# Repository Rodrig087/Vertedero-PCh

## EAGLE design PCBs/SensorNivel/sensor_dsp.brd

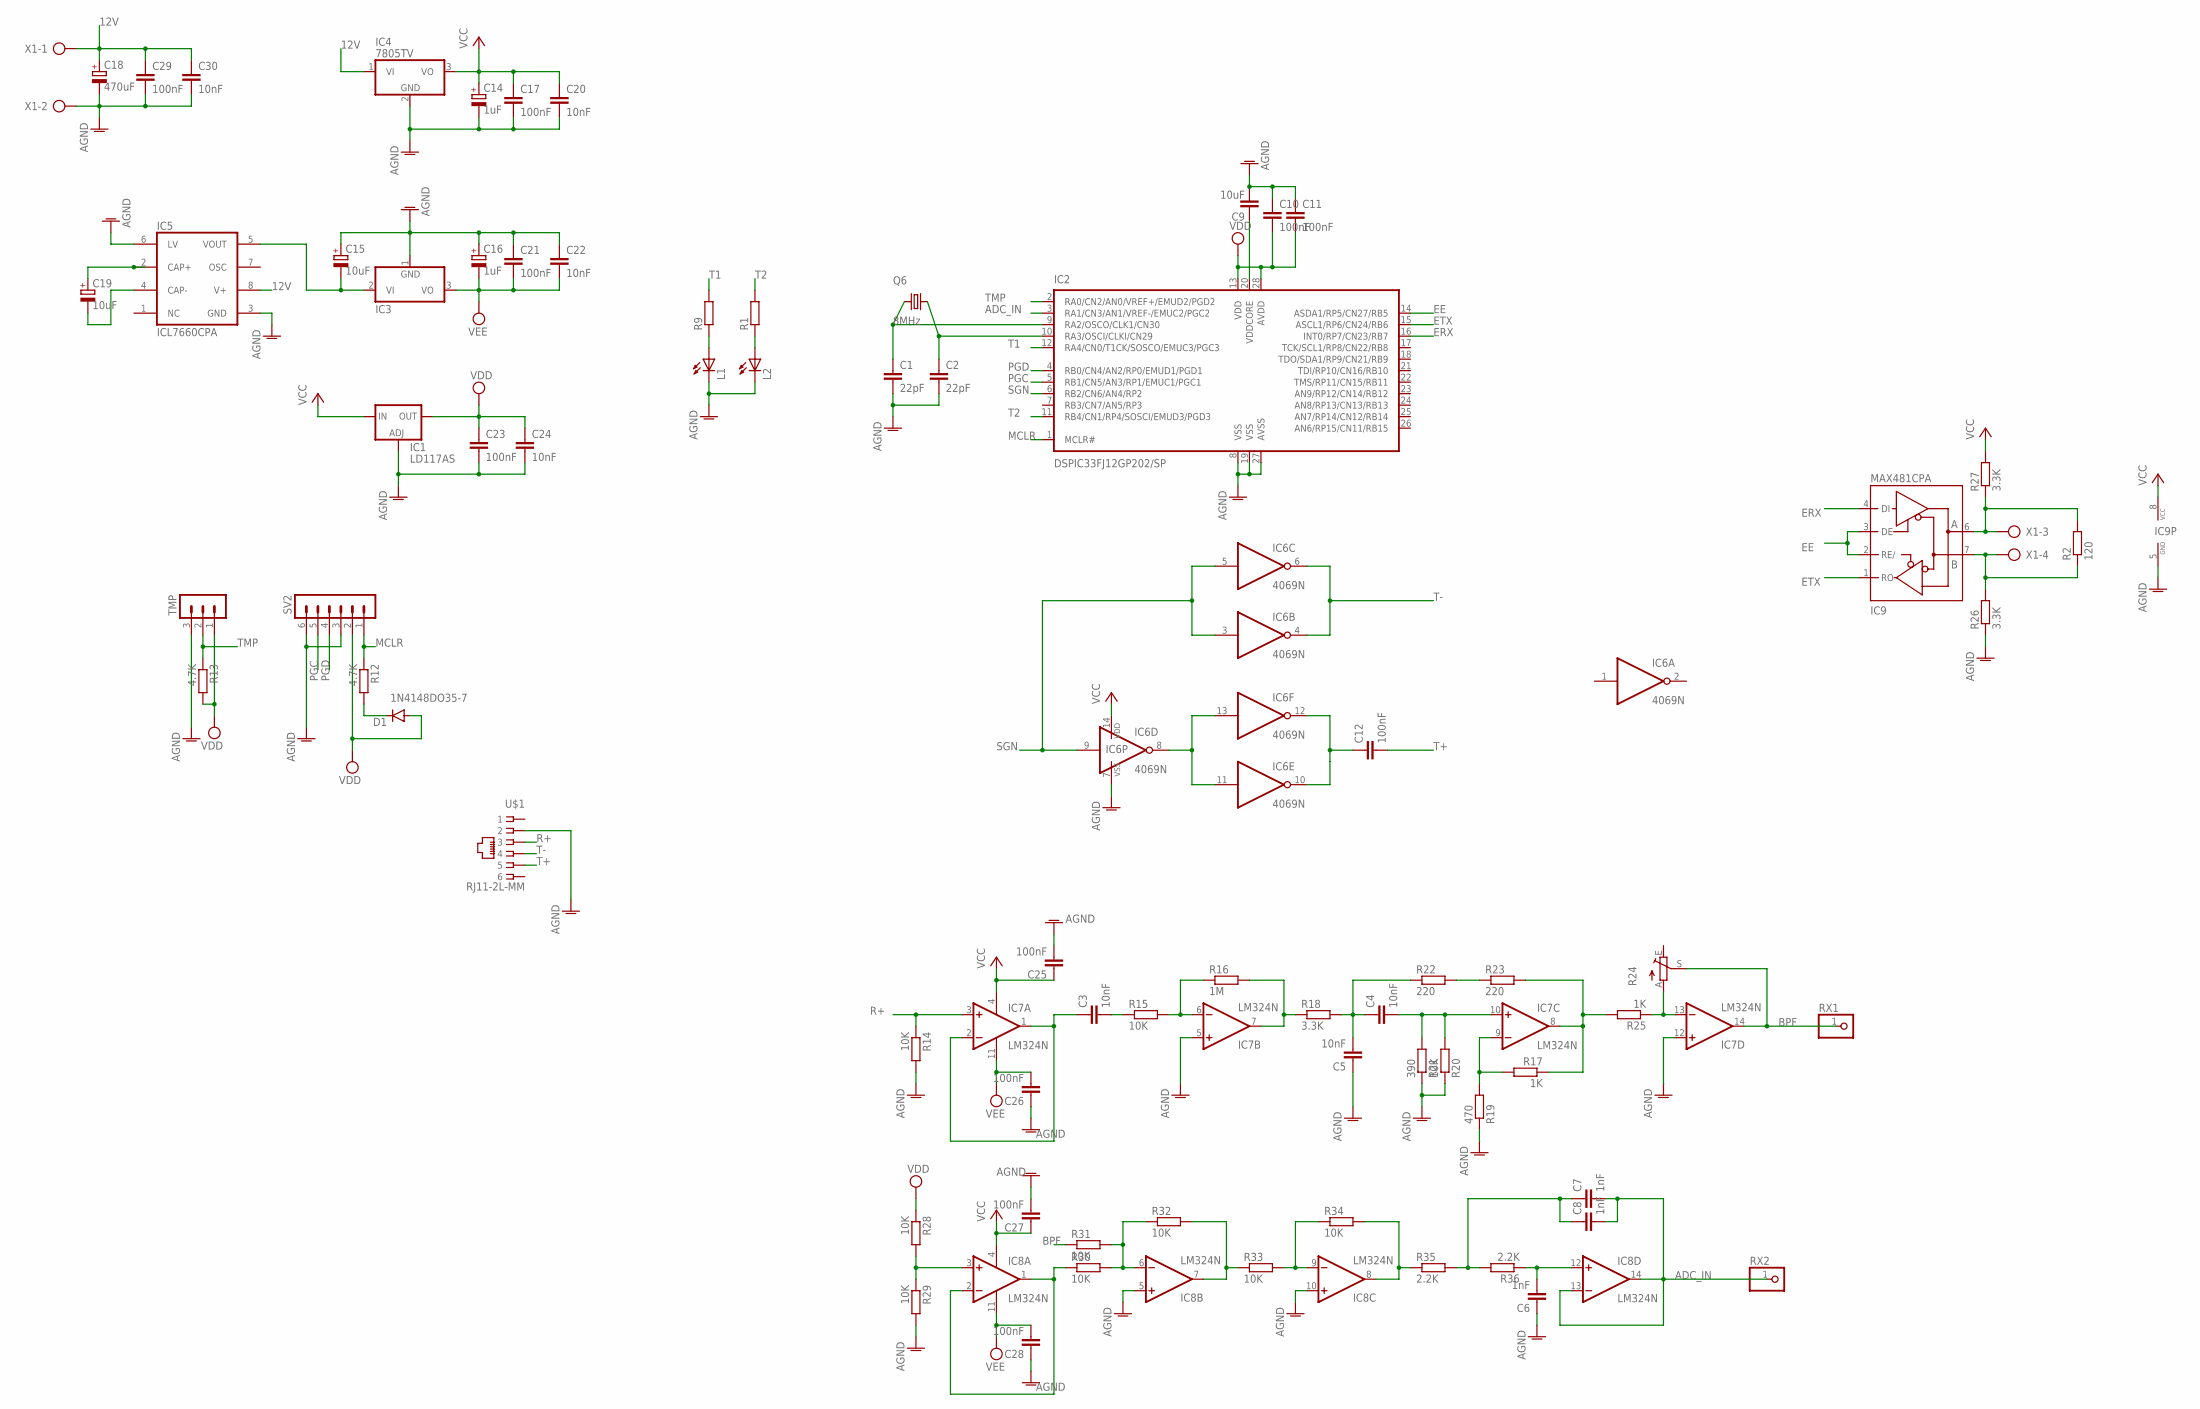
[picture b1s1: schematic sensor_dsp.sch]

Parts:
C1, C2: 22pF; C025-024X044
C3, C4, C5, C20, C22, C24, C30: 10nF; C5B2.5
C6, C7, C8: 1nF; C5B2.5
C9: 10uF; C050-024X044
C10, C11, C12, C17, C21, C23, C25, C26, C27, C28, C29: 100nF; C5B2.5
C14, C16: 1uF; E2,5-5
C15, C19: 10uF; E2,5-5
C18: 470uF; E3,5-8
D1: 1N4148DO35-7; DO35-7
IC1: LD117AS; SOT223
IC2: DSPIC33FJ12GP202/SP; DIL28-3
IC3: 79; TO220V
IC4: 7805TV; TO220V
IC5: ICL7660CPA; DIL08
IC6: 4069N; DIL14
IC7, IC8: LM324N; DIL14
IC9: MAX481CPA; DIL08
L1, L2: LED3MM
Q6: 8MHz; SM49
R1, R9: R-EU_0204/7; 0204/7
R2: 120; 0204/7
R12, R13: 4.7K; 0204/7
R14, R15, R20, R28, R29, R30, R31, R32, R33, R34: 10K; 0204/7
R16: 1M; 0204/7
R17, R25: 1K; 0204/7
R18, R26, R27: 3.3K; 0204/7
R19: 470; 0204/7
R21: 390; 0204/7
R22, R23: 220; 0204/7
R24: TRIM_EU-B64W; B64W
R35, R36: 2.2K; 0204/7
RX1, RX2: PINHD-1X1; 1X01
SV2: MA06-1
TMP: MA03-1
U$1: RJ11-2L-MM; RJ11-NO_SHIELD_2
X1: AK300/4

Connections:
12V: C18.+, C29.1, C30.1, IC4.1 (VI), IC5.8 (V+), X1.1
A: IC9.6 (A), R2.2, R27.1, X1.3
ADC_IN: C7.2, C8.2, IC2.3 (RA1/CN3/AN1/VREF-/EMUC2/PGC2), IC8.13 (-IN), IC8.14 (OUT), RX2.1
AGND: C1.2, C2.2, C5.1, C6.1, C9.2, C10.1, C11.1, C14.-, C15.+, C16.+, C17.2, C18.-, C20.2, C21.1, C22.1, C23.2, C24.2, C25.2, C26.1, C27.2, C28.1, C29.2, C30.2, IC1.1 (ADJ), IC2.8 (VSS), IC2.19 (VSS), IC2.27 (AVSS), IC3.1 (GND), IC4.2 (GND), IC5.3 (GND), IC5.6 (LV), IC6.7 (VSS), IC7.5 (+IN), IC7.12 (+IN), IC8.5 (+IN), IC8.10 (+IN), IC9.5 (GND), L1.K (C), L2.K (C), R14.2, R19.1, R20.1, R21.1, R26.1, R29.2, SV2.3, SV2.6, TMP.3, U$1.2, X1.2
B: IC9.7 (B), R2.1, R26.2, X1.4
BPF: IC7.14 (OUT), R24.S, R31.1, RX1.1
EE: IC2.14 (ASDA1/RP5/CN27/RB5), IC9.2 (RE/), IC9.3 (DE)
ERX: IC2.16 (INT0/RP7/CN23/RB7), IC9.4 (DI)
ETX: IC2.15 (ASCL1/RP6/CN24/RB6), IC9.1 (RO)
MCLR: IC2.1 (MCLR#), R12.1, SV2.1
unnamed: C9.1, IC2.20 (VDDCORE)
unnamed: C19.+, IC5.2 (CAP+)
unnamed: C15.-, IC3.2 (VI), IC5.5 (VOUT)
unnamed: C1.1, IC2.9 (RA2/OSCO/CLK1/CN30), Q6.1
unnamed: C19.-, IC5.4 (CAP-)
unnamed: L1.A, R9.1
unnamed: C3.1, IC7.1 (OUT), IC7.2 (-IN)
unnamed: C2.1, IC2.10 (RA3/OSCI/CLKI/CN29), Q6.2
unnamed: IC7.6 (-IN), R15.2, R16.1
unnamed: D1.C, R12.2
unnamed: IC6.8 (O), IC6.11 (I), IC6.13 (I)
unnamed: C12.1, IC6.10 (O), IC6.12 (O)
unnamed: IC7.7 (OUT), R16.2, R18.1
unnamed: C3.2, R15.1
unnamed: IC7.8 (OUT), R17.1, R23.2, R25.2
unnamed: IC7.9 (-IN), R17.2, R19.2
unnamed: C4.2, IC7.10 (+IN), R20.2, R21.2
unnamed: IC8.1 (OUT), IC8.2 (-IN), R30.1
unnamed: C4.1, C5.2, R18.2, R22.1
unnamed: R22.2, R23.1
unnamed: IC7.13 (-IN), R24.A, R25.1
unnamed: IC8.3 (+IN), R28.2, R29.1
unnamed: IC8.6 (-IN), R30.2, R31.2, R32.1
unnamed: IC8.7 (OUT), R32.2, R33.1
unnamed: IC8.9 (-IN), R33.2, R34.1
unnamed: IC8.8 (OUT), R34.2, R35.1
unnamed: L2.A, R1.1
unnamed: C7.1, C8.1, R35.2, R36.2
unnamed: C6.2, IC8.12 (+IN), R36.1
PGC: IC2.5 (RB1/CN5/AN3/RP1/EMUC1/PGC1), SV2.5
PGD: IC2.4 (RB0/CN4/AN2/RP0/EMUD1/PGD1), SV2.4
R+: IC7.3 (+IN), R14.1, U$1.3
SGN: IC2.6 (RB2/CN6/AN4/RP2), IC6.3 (I), IC6.5 (I), IC6.9 (I)
T1: IC2.12 (RA4/CN0/T1CK/SOSCO/EMUC3/PGC3), R9.2
T2: IC2.11 (RB4/CN1/RP4/SOSCI/EMUD3/PGD3), R1.2
T+: C12.2, U$1.5
T-: IC6.4 (O), IC6.6 (O), U$1.4
TMP: IC2.2 (RA0/CN2/AN0/VREF+/EMUD2/PGD2), R13.1, TMP.2
VCC: C14.+, C17.1, C20.1, C25.1, C27.1, IC1.3 (IN), IC4.3 (VO), IC6.14 (VDD), IC7.4 (V+), IC8.4 (V+), IC9.8 (VCC), R27.2
VDD: C10.2, C11.2, C23.1, C24.1, D1.A, IC1.4 (OUT), IC2.13 (VDD), IC2.28 (AVDD), R13.2, R28.1, SV2.2, TMP.1
VEE: C16.-, C21.2, C22.2, C26.2, C28.2, IC3.3 (VO), IC7.11 (V-), IC8.11 (V-)

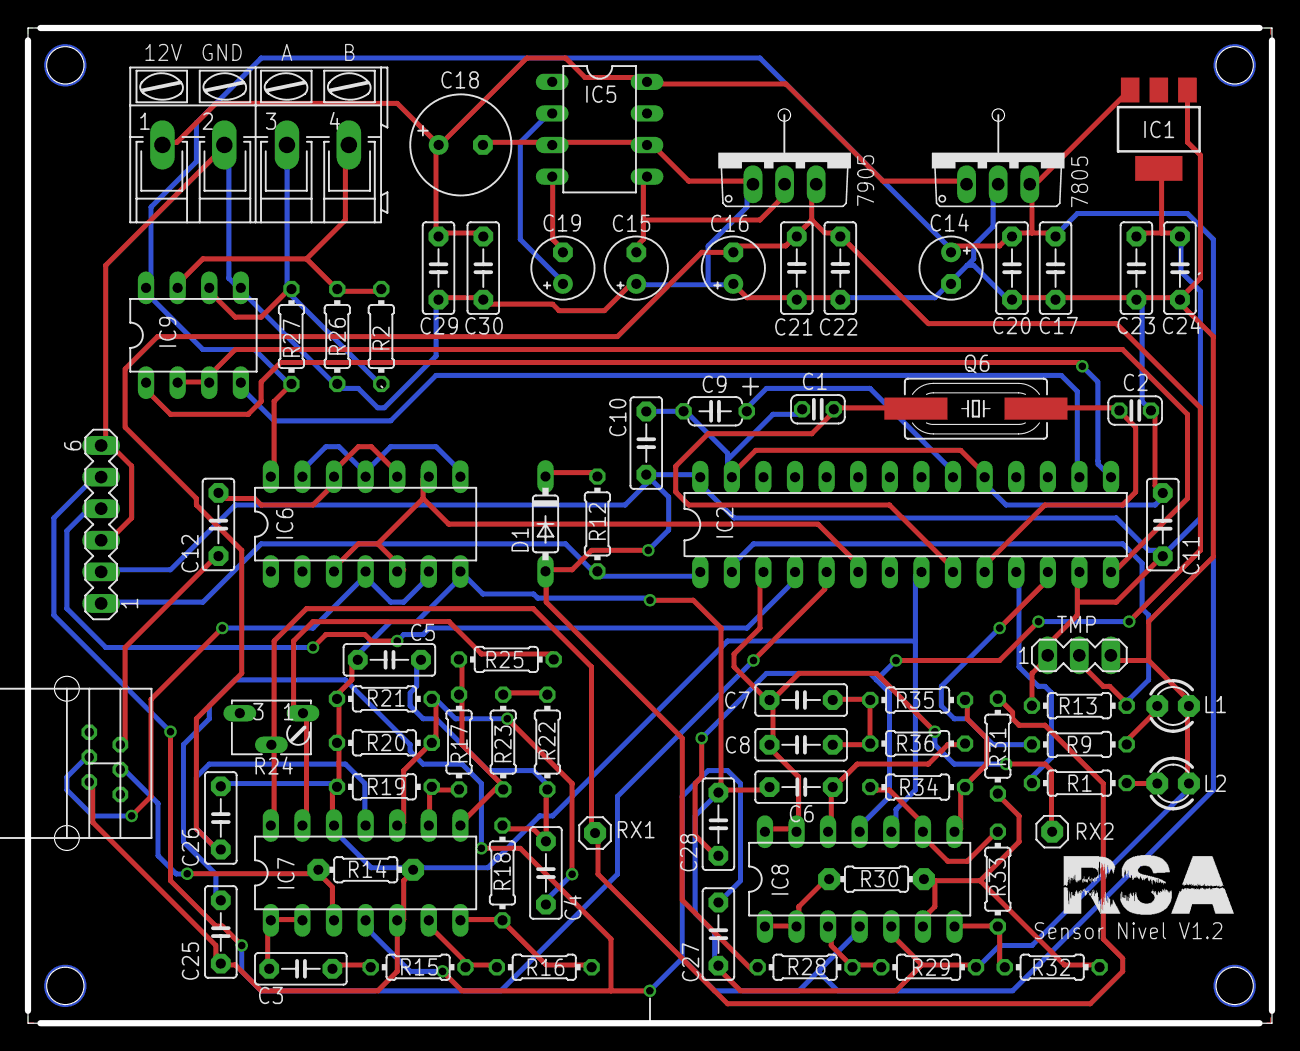
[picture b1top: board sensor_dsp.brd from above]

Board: 2 copper layers, 100.0 x 80.0 mm, 76 parts (0 on the bottom side), 51 nets.

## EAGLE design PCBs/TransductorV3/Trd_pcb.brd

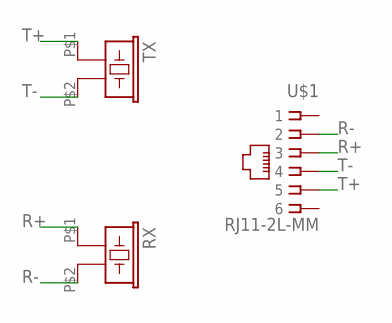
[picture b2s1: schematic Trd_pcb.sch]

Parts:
RX: 400ST/R100; DIA-9.7-5
TX: 400ST/R100; DIA-9.7-5
U$1: RJ11-2L-MM; RJ11-NO_SHIELD_2

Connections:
R+: RX.P$1 (1), U$1.3
R-: RX.P$2 (2), U$1.2
T+: TX.P$1 (1), U$1.5
T-: TX.P$2 (2), U$1.4

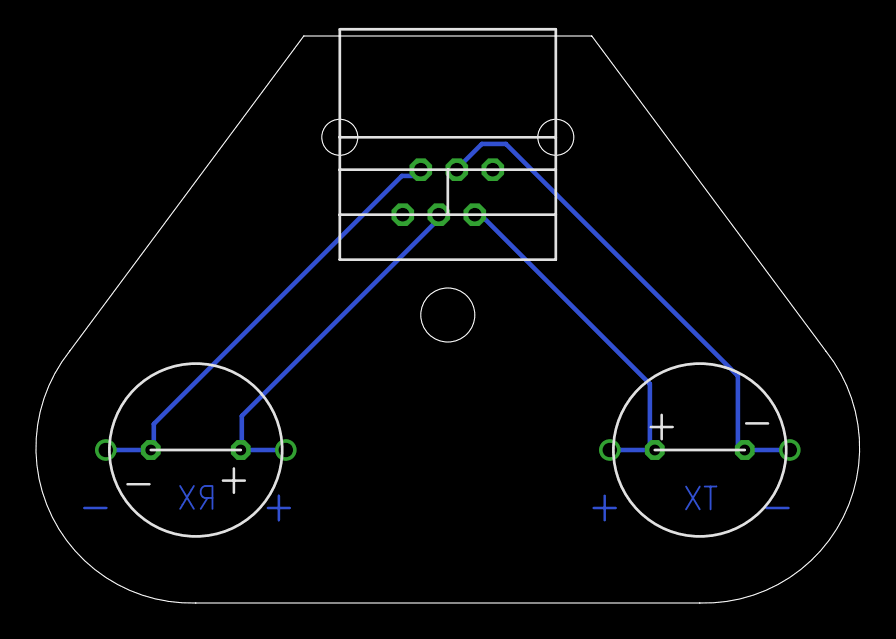
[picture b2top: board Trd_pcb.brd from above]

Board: 2 copper layers, 45.8 x 31.5 mm, 3 parts (0 on the bottom side), 4 nets.

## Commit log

2021-09-09 Inicio
2021-10-06 Se implementaron los PCBs del sensor y el transductor. Se puso en funcionamiento el Firmware del sensor de nivel desarrollado en la tesis, cambiando algunos metodos, y borrando e implementando unos n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
2021-10-12 Se implmento un programa que convierte el vector de enteros de muestras y envolvente en un vector de shorts para enviarlo por RS485. Se encontro que es necesario modificar la libreria de comunicacion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
2021-10-20 Se modifico el firmware del sensor del nivel para trabajar con numeros de datos de 2 bytes. Se comprobo enviando una trama de prueba de 512bytes y funciona bien.
2021-10-25 Se esta trabajando para graficar la señal muestreada y la señal filtrada.
2021-10-25 InspeccionarUltrasonido.c en proceso
2021-10-26 Software en proceso
2021-10-26 Punto de control. No funciona el muestreo. Voy a cambiar la logica del firmware. Parece que el problema es tener la interrupcion de muestreo dentro de la interrupcion de la comunicacion y que la prio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
2021-10-26 VERSION FUNCIONAL
2021-10-27 VERSION INSTALABLE. Se corrigieron las fallas del firmware.
2021-10-27 Se esta implementando un software en Python para obtener la envolvente de la senal ultrasonica.
2021-11-08 Se implementaron unos programas en Python para analisdar la senal ultrasonica y un programa en C para realizar un proceso de medicion del vertedero de forma automatica
2021-11-08 Se pusieron lo archivos en sus directorios correspondientes
2021-11-09 Inicio de ejemplo de correlacion cruzada
2021-11-09 Se completo el programa que calcula el desfase entre la senal medida y una senal de referencia mediante correlacion cruzada. Funciona bien.
2021-11-10 Se agrego un programa de prueba que genera un tren de pulsos y realiza su filtrado pasa-banda para tomarlo como referencia para las mediciones. Se edito el programa CorrelacionUltrasonido.py para agr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
2021-11-12 Se modifico el programa AnalisisTemperatura-Distancia.py para realizar un analisis que permita establecer los valores de calibracion de TOF y temperatura en base a las mediciones de referencia. Luego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
2021-11-15 Se actualizaron los programas CorrelacionUltrasonido y TrenPulsos
2021-11-16 1. Version correlacion para Rpi. 2. Instrucciones de instalacion de scipy, numpy y python 3.8 para Rpi. 3. Inicio calibracion dht22 Arduino.
2021-11-16 Se implemento y modifico un programa en Arduino para leer un sensor DHT22 y un sensor DS18B20 y mostrar sus valores en un LCD-Nokia-5110
2021-11-17 Se corrigio el programa en Arduino LeerSensoresTempHumd y se comprobo que los sensores funcionan bien.
2021-11-17 Se implemento un programa que genera la senal de referencia y la guarda en un archivo binario utilizando las herramientas de numpy
2021-11-19 Se modifico el programa CorrelacionUltrasonido.py para la RPi, para incluir el archivo de referencia.
2021-11-19 Se edito el programa ProcesarUltrasonido.py para mostrar el funcionamiento de los 2 metodos de calculo de TOF mediante deteccion de envolvente. Luego se cambio el nombre de este programa a MetodosDet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
2021-11-22 Se agregaron los planos en CAD de las estructuras metalicas de los vertederos
2021-11-26 Se rediseñaron y corrigieron los diseños de los PCB. Se diseñaron las platinas de los vertederos basadas en las medidas de los soportes.
2022-01-04 Inicio de programa para calcular el nivel a partir de los archivos binarios en W10
2022-01-05 En proceso
2022-01-06 Se termino de implementar el programa que calcula la distancia a partir de los datos de todos los archivos binarios generados por el sensor de nivel
2022-01-06 Se actualizo el programa para graficar y guardar en un archivo de texto los datos de las mediciones de distancia y temperatura a partir de los archivos binarios del sensor de nivel.
2022-03-25 Se hicieron modificaciones al Firmware y al Software. Version funcional.
2022-05-06 Se agregaron programas para calcular la correlacion y para inspeccionar la señal ultrasonica. Version instalada en la presa
2022-05-17 Se modifico el firmware test/SensorNivel para comprobar el funcionamiento del TMR3 (funciona). Se realizaron algunos cambios en el programa LeerDS18.c (no funciona)
